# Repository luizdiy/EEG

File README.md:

Eletroencefalograma (EEG) DIY
Adaptado de https://openeeg.sourceforge.net/

Placa atual

Software

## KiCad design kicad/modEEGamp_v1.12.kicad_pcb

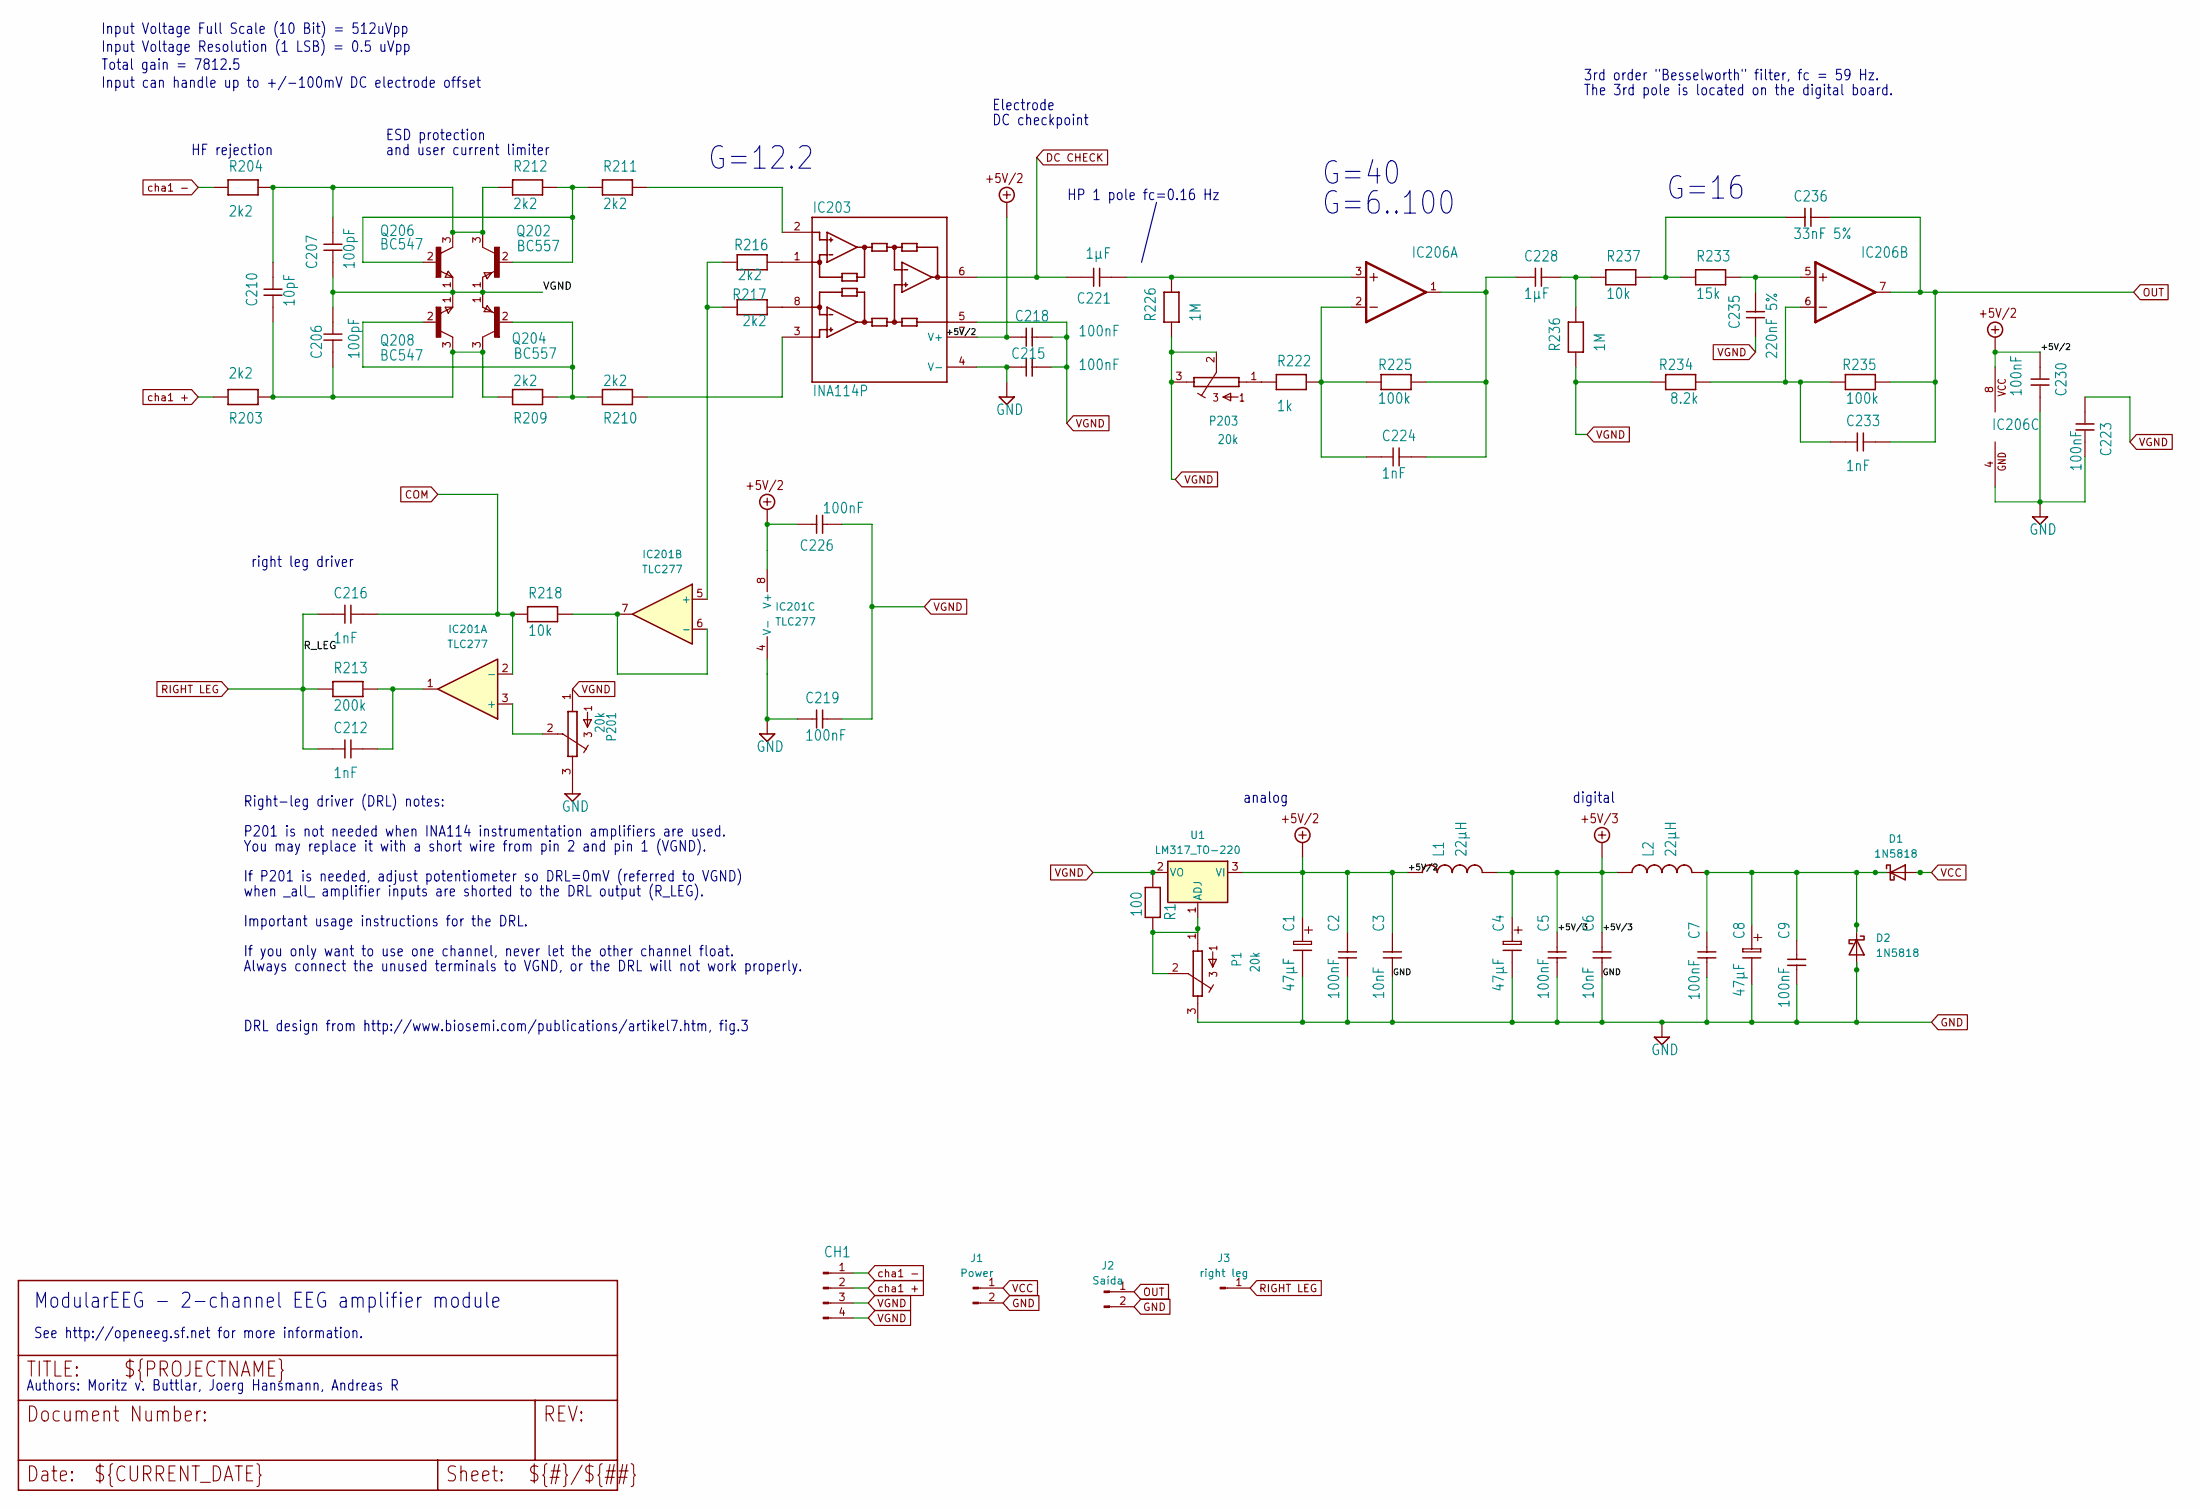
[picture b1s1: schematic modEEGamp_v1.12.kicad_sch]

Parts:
C1, C4, C8: 47µF; CP_Radial_D6.3mm_P2.50mm
C2, C5, C7, C9, C215, C218, C219, C223, C226, C230: 100nF; C-5
C3, C6: 10nF; C-5
C206, C207: 100pF; C-5
C210: 10pF; C-5
C212, C216, C224, C233: 1nF; C-5
C221, C228: 1µF; C-10
C235: 220nF 5%; C-5
C236: 33nF 5%; C-5
CH1: PinHeader_2x02_P2.54mm_Vertical
D1, D2: 1N5818; D_DO-41_SOD81_P7.62mm_Horizontal
IC201: TLC277; DIL-08
IC203: INA114P; DIL-08
IC206: TLC277P; DIL-08
J1: Power; PinHeader_1x02_P2.54mm_Vertical
J2: Saída; PinHeader_1x02_P2.54mm_Vertical
J3: right leg; PinHeader_1x01_P2.54mm_Vertical
L1, L2: 22µH; L_Radial_L7.5mm_W4.6mm_P5.00mm_Neosid_SD75
P1, P201, P203: 20k; S64Y
Q202, Q204: BC557; TO92
Q206, Q208: BC547; TO92
R1: 100; R_Axial_DIN0204_L3.6mm_D1.6mm_P7.62mm_Horizontal
R203, R204, R209, R210, R211, R212, R216, R217: 2k2; R_Axial_DIN0204_L3.6mm_D1.6mm_P7.62mm_Horizontal
R213: 200k; R_Axial_DIN0204_L3.6mm_D1.6mm_P7.62mm_Horizontal
R218, R237: 10k; R_Axial_DIN0204_L3.6mm_D1.6mm_P7.62mm_Horizontal
R222: 1k; R_Axial_DIN0204_L3.6mm_D1.6mm_P7.62mm_Horizontal
R225, R235: 100k; R_Axial_DIN0204_L3.6mm_D1.6mm_P7.62mm_Horizontal
R226, R236: 1M; R_Axial_DIN0204_L3.6mm_D1.6mm_P7.62mm_Horizontal
R233: 15k; R_Axial_DIN0204_L3.6mm_D1.6mm_P7.62mm_Horizontal
R234: 8.2k; R_Axial_DIN0204_L3.6mm_D1.6mm_P7.62mm_Horizontal
U1: LM317_TO-220; TO-220-3_Vertical

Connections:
+5V/2: C1.1, C2.2, C3.2, C218.1, C226.2, C230.2, IC201.8 (V+), IC203.7 (V+), IC206.8 (VCC), L1.1, U1.3 (VI)
+5V/3: C4.1, C5.2, C6.2, L1.2, L2.1
COM: C216.2, IC201.2 (-), R218.1
DC CHECK: C221.2, IC203.6 (OUT)
GND: C1.2, C2.1, C3.1, C4.2, C5.1, C6.1, C7.2, C8.2, C9.1, C215.1, C219.1, C223.1, C230.1, D2.2 (A), IC201.4 (V-), IC203.4 (V-), IC206.4 (GND), J1.2, J2.2, P1.3, P201.3
unnamed: C212.2, IC201.1, R213.2
unnamed: C228.2, R236.2, R237.1
unnamed: C236.1, R233.1, R237.2
unnamed: C7.1, C8.1, C9.2, D1.1 (K), D2.1 (K), L2.2
unnamed: IC201.3 (+), P201.2
unnamed: IC201.5 (+), R216.2, R217.2
unnamed: IC201.6 (-), IC201.7, R218.2
unnamed: IC203.3 (+IN), R210.2
unnamed: IC203.2 (-IN), R211.2
unnamed: IC203.1 (RG), R216.1
unnamed: IC203.8 (RG@1), R217.1
unnamed: C221.1, IC206.3 (+IN), R226.2
unnamed: C224.1, IC206.2 (-IN), R222.2, R225.1
unnamed: C224.2, C228.1, IC206.1 (OUT), R225.2
unnamed: C235.2, IC206.5 (+IN), R233.2
unnamed: C233.1, IC206.6 (-IN), R234.2, R235.1
unnamed: P203.1, R222.1
unnamed: Q202.2 (B), Q206.2 (B), R211.1, R212.2
unnamed: C207.2, C210.2, Q202.3 (C), Q206.3 (C), R204.2, R212.1
unnamed: Q204.2 (B), Q208.2 (B), R209.2, R210.1
unnamed: C206.1, C210.1, Q204.3 (C), Q208.3 (C), R203.2, R209.1
unnamed: P1.1, P1.2, R1.1, U1.1 (ADJ)
OUT: C233.2, C236.2, IC206.7 (OUT), J2.1, R235.2
RIGHT LEG: C212.1, C216.1, J3.1, R213.1
VCC: D1.2 (A), J1.1
VGND: C206.2, C207.1, C215.2, C218.2, C219.2, C223.2, C226.1, C235.1, CH1.3, CH1.4, IC203.5 (REF), P201.1, P203.2, P203.3, Q202.1 (E), Q204.1 (E), Q206.1 (E), Q208.1 (E), R1.2, R226.1, R234.1, R236.1, U1.2 (VO)
cha1 +: CH1.2, R203.1
cha1 -: CH1.1, R204.1

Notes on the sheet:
Right-leg driver (DRL) notes:
Important usage instructions for the DRL.
G=12.2
digital
G=16
when _all_ amplifier inputs are shorted to the DRL output (R_LEG).
Always connect the unused terminals to VGND, or the DRL will not work properly.
Input Voltage Full Scale (10 Bit) = 512uVpp
Electrode
and user current limiter
G=40
3rd order "Besselworth" filter, fc = 59 Hz.
HP 1 pole fc=0.16 Hz
DC checkpoint
See http://openeeg.sf.net for more information.
P201 is not needed when INA114 instrumentation amplifiers are used.
Input can handle up to +/-100mV DC electrode offset
DRL design from http://www.biosemi.com/publications/artikel7.htm, fig.3
HF rejection
Authors: Moritz v. Buttlar, Joerg Hansmann, Andreas R
ESD protection
analog
G=6..100
Total gain = 7812.5
Input Voltage Resolution (1 LSB) = 0.5 uVpp
If P201 is needed, adjust potentiometer so DRL=0mV (referred to VGND)
If you only want to use one channel, never let the other channel float.
The 3rd pole is located on the digital board.
You may replace it with a short wire from pin 2 and pin 1 (VGND).
right leg driver
ModularEEG - 2-channel EEG amplifier module

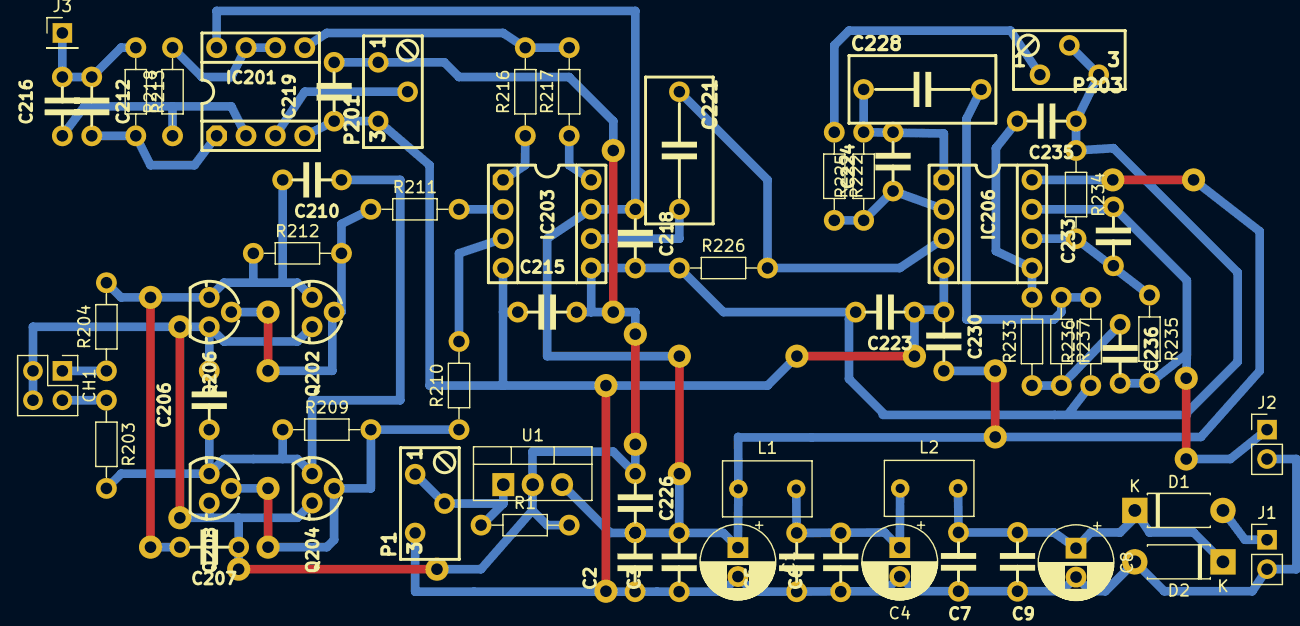
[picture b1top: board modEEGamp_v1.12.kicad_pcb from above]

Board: 2 copper layers, 64 parts (0 on the bottom side), 33 nets.

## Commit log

2024-06-27 teste
2024-06-28 pequenas correções
2024-07-03 Funcionalidade Análise de sinal incluida
2024-07-03 incluido exemplo
2024-07-04 Ajustes na exibição dos gráficos
2024-07-13 alteração local dados
2024-07-16 foto
2024-07-16 nomes de arquivos
